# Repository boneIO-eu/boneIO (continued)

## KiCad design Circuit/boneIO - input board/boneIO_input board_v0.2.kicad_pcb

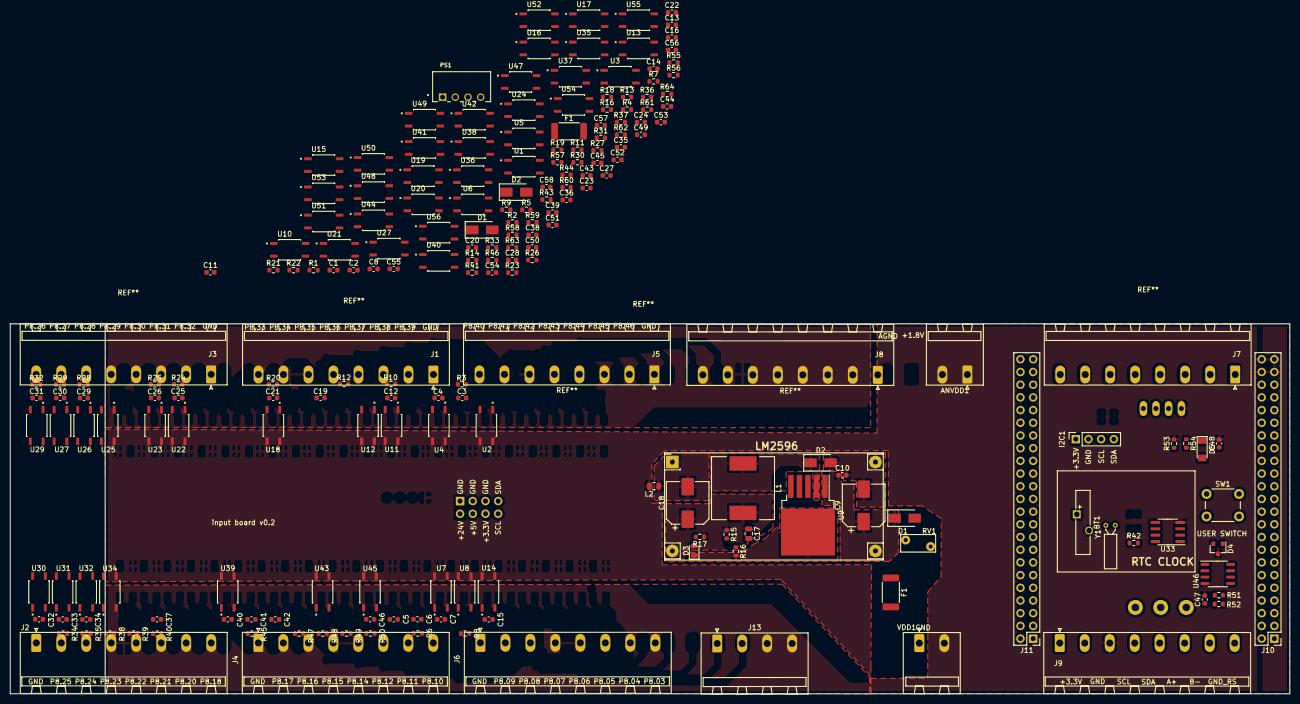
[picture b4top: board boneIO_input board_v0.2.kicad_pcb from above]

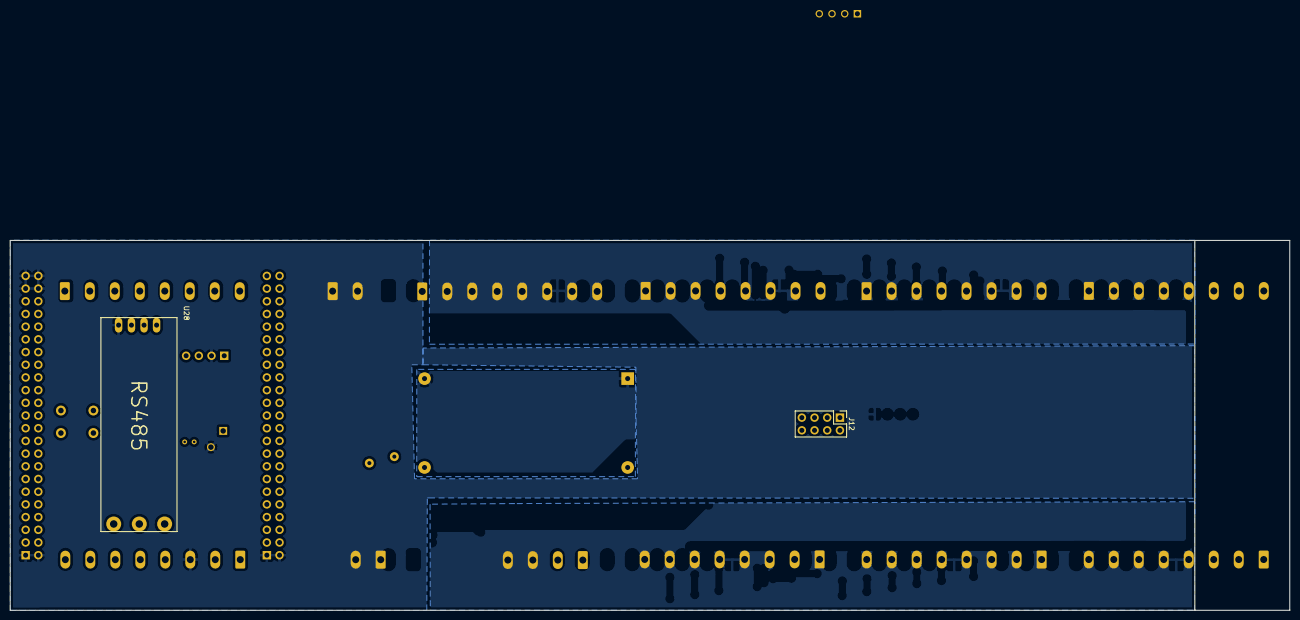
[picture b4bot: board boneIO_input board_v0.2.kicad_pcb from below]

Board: 2 copper layers, 256.0 x 74.0 mm, 212 parts (2 on the bottom side), 190 nets, no tracks yet.

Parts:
ANVDD1: Screw_Terminal_01x02; Phoenix_1x02_P5.00mm_Horizontal
BT1: Battery; Battery_Panasonic_CR1220-VCN_Vertical_CircularHoles
C1, C2, C3, C4, C5, C6, C7, C8, C10, C11, C12, C13, C14, C15, C16, C19, C20, C21, C22, C23, C24, C25, C26, C27, C28, C29, C30, C31, C32, C33, C34, C35, C36, C37, C38, C39, C40, C41, C42, C43, C44, C45, C46, C47, C48, C49, C50, C51, C52, C53, C54, C55, C56, C57, C58: 100n; C_0603_1608Metric
C9: 100uF/50V; CP_Elec_8x10
C17: 3n3; C_0805_2012Metric
C18: 220u/35V; CP_Elec_8x10
D1, D1#2: B340A-13F; D_SMA
D2, D2#2: SS34; D_SMA
D3: LED_RED; LED_0805_2012Metric
D4: BAT54A; SOT-23
D5: 1N4148; D_MiniMELF
F1, F1#2: Fuse_3A; Fuse_2512_6332Metric
I2C1: Conn_01x04; PinSocket_1x04_P2.54mm_Vertical
J1, J2, J3, J4, J5, J6, J7, J8, J9: Screw_Terminal_01x08; 8pin
J10, J11: BeagleBone_Black_Header; PinHeader_2x23_P2.54mm_Vertical
J12: Conn_02x04_Odd_Even; PinHeader_2x04_P2.54mm_Vertical
J13: Screw_Terminal_01x04; Phoenix_1x04_P5.00mm_Horizontal
L1: 4.7uH; L_12x12mm_H6mm
L2: BLM21PG221SN1D; L_0805_2012Metric
PS1: B2424S-1WR2; CONV_B0505S-1WR2
R1, R2, R3, R4, R5, R6, R7, R8, R9, R10, R11, R12, R13, R14, R18, R19, R20, R21, R22, R23, R24, R25, R26, R27, R28, R29, R32, R33, R34, R35, R36, R37, R38, R39, R40, R41, R42, R43, R44, R45, R46, R47, R48, R49, R50, R55, R56, R57, R58, R59, R60, R61, R62, R63, R64: 10k; R_0603_1608Metric
R15: 3k; R_0603_1608Metric
R16, R16#2, R17: 1k; R_0603_1608Metric
R30, R31, R54: 4.7k; R_0603_1608Metric
R51, R52: 680R; R_0603_1608Metric
R53: 330R; R_0603_1608Metric
RV1: 07D270K; RV_Disc_D7mm_W3.5mm_P5mm
SW1: SW_Push; SW_PUSH_6mm_H13mm
U1, U2, U3, U4, U5, U6, U7, U8, U10, U11, U12, U13, U14, U15, U16, U17, U18, U19, U20, U21, U22, U23, U24, U25, U26, U27, U27#2, U29, U30, U31, U32, U34, U35, U36, U37, U38, U39, U40, U41, U42, U43, U44, U45, U47, U48, U49, U50, U51, U52, U53, U54, U55, U56: EL357N-G; OPTO_EL357N-G
U9: LM2596S-ADJ; TO-263-5_TabPin3
U28: RS485; RS485_moduleTTL
U33: DS1307Z+; SOIC-8_3.9x4.9mm_P1.27mm
U46: P82B96; SO-8_3.9x4.9mm_P1.27mm
VDD1: Screw_Terminal_01x02; Phoenix_1x02_P5.00mm_Horizontal
Y1: 32,788 MHz; Crystal_C26-LF_D2.1mm_L6.5mm_Horizontal

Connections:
+3V3: C47.1, D5.1, I2C1.1, J9.2, J10.3, J10.4, J12.6, R30.1, R31.1, R36.1, R37.1, R42.1, R51.1, R52.1, R54.1, U28.1, U33.8, U46.8
+5V: C17.1, C18.1, J9.1, J10.5, J10.6, J12.4, L1.2, R15.1, R17.1
+24V: C9.1, C10.1, D1.1, D1#2.1, J12.2, PS1.2, U9.1
+24VA: PS1.4, R1.2, R2.2, R3.2, R4.2, R5.2, R6.2, R7.2, R8.2, R9.2, R10.2, R11.2, R12.2, R13.2, R14.2, R18.2, R19.2, R20.2, R21.2, R22.2, R23.2, R24.2, R25.2, R26.2, R27.2, R28.2, R29.2, R32.2, R33.2, R34.2, R35.2, R38.2, R39.2, R40.2, R41.2, R43.2, R44.2, R45.2, R46.2, R47.2, R48.2, R49.2, R50.2, R55.2, R56.2, R57.2, R58.2, R59.2, R60.2, R61.2, R62.2, R63.2, R64.2
A+: J9.6, U28.5
B-: J9.7, U28.6
Earth: C9.2, C10.2, C18.2, D2.2, D2#2.2, D3.1, L2.1, R16.2, R16#2.2, RV1.2, U9.3, U9.5, VDD1.2
GND: BT1.2, C47.2, C48.2, D4.3, I2C1.2, J8.1, J9.3, J10.1, J10.2, J10.43, J10.44, J10.45, J10.46, J11.1, J11.2, J12.1, J12.3, J12.5, J13.1, L2.2, PS1.1, R53.2, U1.3, U2.3, U3.3, U4.3, U5.3, U6.3, U7.3, U8.3, U10.3, U11.3, U12.3, U13.3, U14.3, U15.3, U16.3, U17.3, U18.3, U19.3, U20.3, U21.3, U22.3, U23.3, U24.3, U25.3, U26.3, U27.3, U27#2.3, U28.4, U29.3, U30.3, U31.3, U32.3, U33.4, U34.3, U35.3, U36.3, U37.3, U38.3, U39.3, U40.3, U41.3, U42.3, U43.3, U44.3, U45.3, U46.4, U47.3, U48.3, U49.3, U50.3, U51.3, U52.3, U53.3, U54.3, U55.3, U56.3
GNDA: J1.1, J2.1, J3.1, J4.1, J5.1, J6.1, PS1.3
GNDD: J9.8, U28.7
GND_ADC: ANVDD1.2, J10.34
unnamed: BT1.1, U33.3
unnamed: C1.1, R1.1, U1.1
unnamed: C2.1, R2.1, U2.1
unnamed: C3.1, R3.1, U3.1
unnamed: C4.1, R4.1, U4.1
unnamed: C5.1, R5.1, U5.1
unnamed: C6.1, R6.1, U6.1
unnamed: C7.1, R7.1, U7.1
unnamed: C8.1, R8.1, U8.1
unnamed: C11.1, R9.1, U10.1
unnamed: C12.1, R10.1, U11.1
unnamed: C13.1, R11.1, U12.1
unnamed: C14.1, R12.1, U13.1
unnamed: C15.1, R13.1, U14.1
unnamed: C16.1, R14.1, U15.1
unnamed: C17.2, R15.2, R16.1, R16#2.1, U9.4
unnamed: C19.1, R18.1, U16.1
unnamed: C20.1, R19.1, U17.1
unnamed: C21.1, R20.1, U18.1
unnamed: C22.1, R21.1, U19.1
unnamed: C23.1, R22.1, U20.1
unnamed: C24.1, R23.1, U21.1
unnamed: C25.1, R24.1, U22.1
unnamed: C26.1, R25.1, U23.1
unnamed: C27.1, R26.1, U24.1
unnamed: C28.1, R27.1, U25.1
unnamed: C29.1, R28.1, U26.1
unnamed: C30.1, R29.1, U27.1, U27#2.1
unnamed: C31.1, R32.1, U29.1
unnamed: C32.1, R33.1, U30.1
unnamed: C33.1, R34.1, U31.1
unnamed: C34.1, R35.1, U32.1
unnamed: C35.1, R38.1, U34.1
unnamed: C36.1, R39.1, U35.1
unnamed: C37.1, R40.1, U36.1
unnamed: C38.1, R41.1, U37.1
unnamed: C39.1, R43.1, U38.1
unnamed: C40.1, R44.1, U39.1
unnamed: C41.1, R45.1, U40.1
unnamed: C42.1, R46.1, U41.1
unnamed: C43.1, R47.1, U42.1
unnamed: C44.1, R48.1, U43.1
unnamed: C45.1, R49.1, U44.1
unnamed: C46.1, R50.1, U45.1
unnamed: C49.1, R55.1, U47.1
unnamed: C50.1, R56.1, U48.1
unnamed: C51.1, R57.1, U49.1
unnamed: C52.1, R58.1, U50.1
unnamed: C53.1, R59.1, U51.1
unnamed: C54.1, R60.1, U52.1
unnamed: C55.1, R61.1, U53.1
unnamed: C56.1, R62.1, U54.1
unnamed: C57.1, R63.1, U55.1
unnamed: C58.1, R64.1, U56.1
unnamed: D1.2, D1#2.2, F1.1, F1#2.1, RV1.1
unnamed: D2.1, D2#2.1, L1.1, U9.2
unnamed: D3.2, R17.2
unnamed: R42.2, U33.7
unnamed: R53.1, SW1.1
unnamed: U33.1, Y1.1
unnamed: U33.2, Y1.2
P8.07: J11.7, U6.4
P8.07_OUT: C6.2, J6.4, U6.2
P8.08: J11.8, U5.4
P8.08_OUT: C5.2, J6.3, U5.2
P8.09: J11.9, U45.4
P8.09_OUT: C46.2, J6.2, U45.2
P8.10: J11.10, U44.4
P8.10_OUT: C45.2, J4.8, U44.2
P8.11: J11.11, U43.4
P8.11_OUT: C44.2, J4.7, U43.2
P8.12: J11.12, U42.4
P8.12_OUT: C43.2, J4.6, U42.2
P8.14: J11.14, U41.4
P8.14_OUT: C42.2, J4.5, U41.2
P8.15: J11.15, U40.4
P8.15_OUT: C41.2, J4.4, U40.2
P8.16: J11.16, U39.4
P8.16_OUT: C40.2, J4.3, U39.2
P8.17: J11.17, U38.4
P8.17_OUT: C39.2, J4.2, U38.2
P8.18: J11.18, U37.4
P8.18_OUT: C38.2, J2.8, U37.2
P8.26: J11.26, U29.4
P8.26_OUT: C31.2, J3.8, U29.2
P8.27: J11.27, U27.4, U27#2.4
P8.27_OUT: C30.2, J3.7, U27.2, U27#2.2
P8.28: J11.28, U26.4
P8.28_OUT: C29.2, J3.6, U26.2
P8.29: J11.29, U25.4
P8.29_OUT: C28.2, J3.5, U25.2
P8.30: J11.30, U24.4
P8.30_OUT: C27.2, J3.4, U24.2
P8.31: J11.31, U23.4
P8.31_OUT: C26.2, J3.3, U23.2
P8.32: J11.32, U22.4
P8.32_OUT: C25.2, J3.2, U22.2
P8.33: J11.33, U21.4
P8.33_OUT: C24.2, J1.8, U21.2
P8.34: J11.34, U20.4
P8.34_OUT: C23.2, J1.7, U20.2
P8.35: J11.35, U19.4
P8.35_OUT: C22.2, J1.6, U19.2
P8.36: J11.36, U18.4
P8.36_OUT: C21.2, J1.5, U18.2
P8.37: J11.37, U17.4
P8.37_OUT: C20.2, J1.4, U17.2
P8.38: J11.38, U16.4
P8.38_OUT: C19.2, J1.3, U16.2
P8.39: J11.39, U13.4
P8.39_OUT: C14.2, J1.2, U13.2
P8.40: J11.40, U12.4
P8.40_OUT: C13.2, J5.8, U12.2
P8.41: J11.41, U11.4
P8.41_OUT: C12.2, J5.7, U11.2
P8.42: J11.42, U10.4
P8.42_OUT: C11.2, J5.6, U10.2
P8.43: J11.43, U4.4
P8.43_OUT: C4.2, J5.5, U4.2
P8.44: J11.44, U3.4
P8.44_OUT: C3.2, J5.4, U3.2
P8.45: J11.45, U2.4
P8.45_OUT: C2.2, J5.3, U2.2
P8.46: J11.46, U1.4
P8.46_OUT: C1.2, J5.2, U1.2
P9.11: J10.11, U34.4
P9.11_OUT: C35.2, J2.2, U34.2
P9.12: J10.12, U35.4
P9.12_OUT: C36.2, J2.3, U35.2
P9.13: J10.13, U36.4
P9.13_OUT: C37.2, J2.4, U36.2
P9.14: J10.14, U7.4
P9.14_OUT: C7.2, J2.5, U7.2
P9.15: J10.15, U8.4
P9.15_OUT: C8.2, J2.6, U8.2
P9.16: J10.16, U30.4
P9.16_OUT: C32.2, J2.7, U30.2
P9.17: J10.17, U31.4
P9.17_OUT: C33.2, J8.8, U31.2
P9.18: J10.18, U32.4
P9.18_OUT: C34.2, J13.2, U32.2
P9.21: J10.21, U14.4
P9.21_OUT: C15.2, J13.3, U14.2
P9.22: J10.22, U15.4
P9.22_OUT: C16.2, J13.4, U15.2
P9.23: J10.23, U51.4
P9.23_OUT: C53.2, J8.7, U51.2
P9.24_OUT: C52.2, J8.6, U50.2
P9.25: J10.25, U49.4
P9.25_OUT: C51.2, J8.5, U49.2
P9.26_OUT: C50.2, J8.4, U48.2
P9.27: J10.27, U47.4
P9.27_OUT: C49.2, J8.3, U47.2
P9.28: J10.28, U56.4
P9.28_OUT: C58.2, J8.2, U56.2
P9.29: J10.29, U55.4
P9.29_OUT: C57.2, J6.8, U55.2
P9.30: J10.30, U54.4
P9.30_OUT: C56.2, J6.7, U54.2
P9.31: J10.31, U53.4
P9.31_OUT: C55.2, J6.6, U53.2
P9.33: J7.7, J10.33
P9.35: J7.5, J10.35
P9.36: J7.6, J10.36
P9.37: J7.3, J10.37
P9.38: J7.4, J10.38
P9.39: J7.1, J10.39
P9.40: J7.2, J10.40
P9.41: C48.1, D5.2, J10.41, R54.2, SW1.2
P9.42: J10.42, U52.4
P9.42_OUT: C54.2, J6.5, U52.2
RX: J10.26, U28.3
SCL: I2C1.3, J10.19, J12.8, R30.2, R37.2, U33.6, U46.7
SCL_OUT: D4.1, J9.5, R51.2, U46.5, U46.6
SDA: I2C1.4, J10.20, J12.7, R31.2, R36.2, U33.5, U46.1
SDA_OUT: D4.2, J9.4, R52.2, U46.2, U46.3
TX: J10.24, U28.2
VCC: F1.2, F1#2.2, VDD1.1
VDD_ADC: ANVDD1.1, J10.32

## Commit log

2021-10-17 change comment
2021-10-21 0.0.1 asyncio version of boneio
2021-10-21 fix requirements
2021-10-22 switch to Adafruit/non working
2021-10-22 fix relay discover
2021-11-02 Zmiana Nazwy płytki
2021-11-02 Revert "Zmiana Nazwy płytki"
    This reverts commit 4cfb8962ad837d49dd7d8c96a90ff7a4eda2ea33.
2021-11-16 Correction
    Corrected relay symbol on RM85-2011-35-1024
2021-11-19 adding 3d models
2021-11-19 correcting the scheme
2021-12-13 Create dok
2021-12-13 Create Documentation
2021-12-13 Create d
2021-12-13 Create a
2021-12-20 Add files via upload
    bez J...
2022-09-11 add gregd
2022-09-26 Input board ESP v0.4
